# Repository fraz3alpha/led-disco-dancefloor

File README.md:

# led-disco-dancefloor

Welcome to the LED Disco Dance Floor project!

As seen at:

- Oggcamp 2017
- LJC Mad Scientists 2016

## Overview

The dancefloor project was conceived, as all good ideas are, at the pub.
The plan was to create a fully illuminated dancefloor, as a surpise, for the
wedding of two of my good friends; Gav & Anna.

The timeline from conception (pub) to completion (wedding) was roughly 8 months
between July of 2013 and the wedding in February 2014. Ideas were bounced around,
rejected, reworked, costed, rejected, reworked, and reworked some more over the
summer, and construction began in earnest November, and continued for 3 solid
months.

The result was a dancefloor consisting of 432 illuminated tiles, each 6"x6" (
because wood comes in feet and inches) creating an usable dancing area of 12'x9'.
The dancefloor was split into 9 modules (for transportation reasons), each coming
in at 4'x3' and about 15kg.

Patterns were created via a connected laptop via the included python program
to be displayed on each module by an ATMega328 microcontroller & TLC5940 constant
current LED drivers.

## The Software

The python software is available in `software/controller/`, and can be run with
or without an attached dancefloor for demonstration and testing purposes.

The software makes use of the **pygame** library to read input from connected joypads
and keyboards, as well as draw the GUI and handle the framerate. If a dancefloor
is connected, **pyserial** is used to send the data at 1Mbps

## The PCB & Firmware

The PCB is relatively simple and is only concerned with the action of parsing
incoming data via a serial connection and displaying it on the 48 connected RGB
LEDs. An ATMega328 is used as the microcontroller, and 3xTLC5940 ICs are used
to drive 16 LEDs each. Each of the Red, Green, and Blue LEDs are strobed, and
the switching is handled via 3 p-channel MOSFETs.

The firmware is written to be flashed using the Arduino IDE for convenience, but
uses very few of the Arduino library convenience functions (`random()`, which is
used in the failsafe backup pattern, being the exception) as most of the tight
loop is highly optimised for speed.

## Power

The entire dancefloor runs off 5v, and requires a high current power supply -
roughly 2.5A per module. An old ATX power supply with all the 5v rails tied
together has proved very reliable.

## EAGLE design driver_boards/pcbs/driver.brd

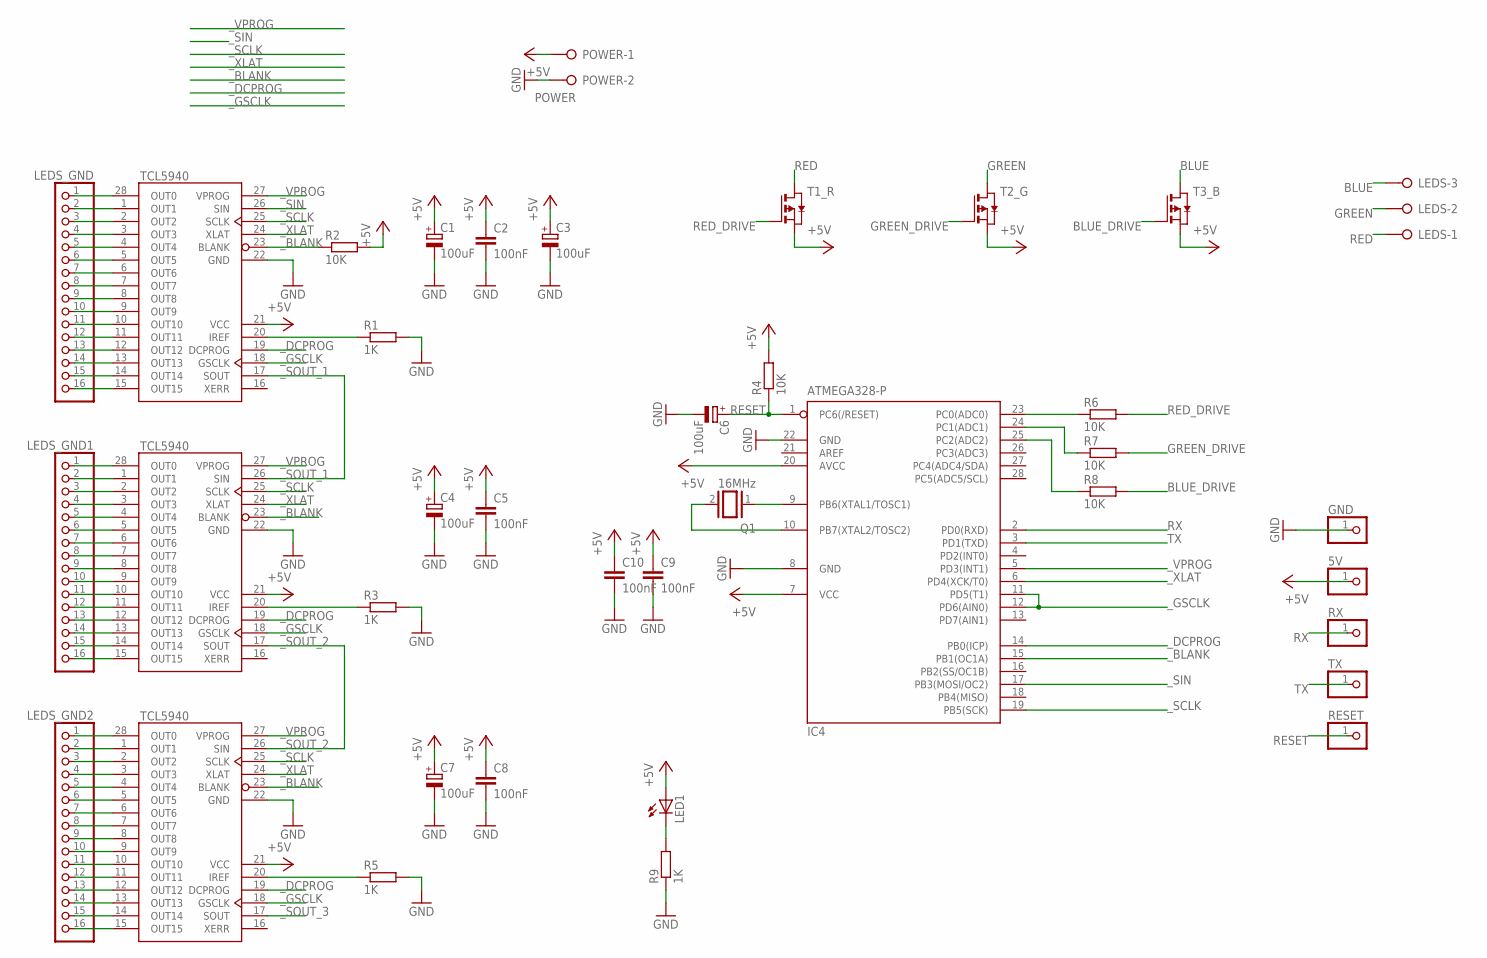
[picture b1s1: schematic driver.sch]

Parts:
5V: PINHD-1X1; 1X01
C1, C3, C4, C6, C7: 100uF; E2,5-6
C2, C5, C8, C9, C10: 100nF; C025-025X050
GND: PINHD-1X1; 1X01
IC4: ATMEGA328-P; DIL28-3
LED1: LED5MM
LEDS: W237-3E
LEDS_GND, LEDS_GND1, LEDS_GND2: PINHD-1X16; 1X16
POWER: POWER; W237-132
Q1: 16MHz; QS
R1, R3, R5, R9: 1K; M0805
R2, R4, R6, R7, R8: 10K; M0805
RESET: PINHD-1X1; 1X01
RX: PINHD-1X1; 1X01
T1_R, T2_G, T3_B: PMOSSOT23; SOT-23
TCL5940_1: TCL5940; DIP28
TLC5940_2, TLC5940_3: TCL5940; DIP28
TX: PINHD-1X1; 1X01

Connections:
+5V: 5V.1, C1.+, C2.1, C3.+, C4.+, C5.1, C7.+, C8.1, C9.1, C10.1, IC4.7 (VCC), IC4.20 (AVCC), LED1.A, POWER.1, R2.2, R4.2, T1_R.2 (S), T2_G.2 (S), T3_B.2 (S), TCL5940_1.21 (VCC), TLC5940_2.21 (VCC), TLC5940_3.21 (VCC)
BLUE: LEDS.3, T3_B.1 (D)
BLUE_DRIVE: R8.2, T3_B.3 (G)
GND: C1.-, C2.2, C3.-, C4.-, C5.2, C6.-, C7.-, C8.2, C9.2, C10.2, GND.1, IC4.8 (GND), IC4.22 (GND), POWER.2, R1.2, R3.2, R5.2, R9.1, TCL5940_1.22 (GND), TLC5940_2.22 (GND), TLC5940_3.22 (GND)
GREEN: LEDS.2, T2_G.1 (D)
GREEN_DRIVE: R7.2, T2_G.3 (G)
unnamed: R1.1, TCL5940_1.20 (IREF)
unnamed: LEDS_GND.1, TCL5940_1.28 (OUT0)
unnamed: LEDS_GND.2, TCL5940_1.1 (OUT1)
unnamed: LEDS_GND.3, TCL5940_1.2 (OUT2)
unnamed: LEDS_GND.4, TCL5940_1.3 (OUT3)
unnamed: LEDS_GND.5, TCL5940_1.4 (OUT4)
unnamed: LEDS_GND.6, TCL5940_1.5 (OUT5)
unnamed: LEDS_GND.7, TCL5940_1.6 (OUT6)
unnamed: LEDS_GND.8, TCL5940_1.7 (OUT7)
unnamed: LEDS_GND.9, TCL5940_1.8 (OUT8)
unnamed: LEDS_GND.10, TCL5940_1.9 (OUT9)
unnamed: LEDS_GND.11, TCL5940_1.10 (OUT10)
unnamed: LEDS_GND.12, TCL5940_1.11 (OUT11)
unnamed: LEDS_GND.13, TCL5940_1.12 (OUT12)
unnamed: LEDS_GND.14, TCL5940_1.13 (OUT13)
unnamed: LEDS_GND.15, TCL5940_1.14 (OUT14)
unnamed: LEDS_GND.16, TCL5940_1.15 (OUT15)
unnamed: R3.1, TLC5940_2.20 (IREF)
unnamed: LEDS_GND1.1, TLC5940_2.28 (OUT0)
unnamed: LEDS_GND1.2, TLC5940_2.1 (OUT1)
unnamed: LEDS_GND1.3, TLC5940_2.2 (OUT2)
unnamed: LEDS_GND1.4, TLC5940_2.3 (OUT3)
unnamed: LEDS_GND1.5, TLC5940_2.4 (OUT4)
unnamed: LEDS_GND1.6, TLC5940_2.5 (OUT5)
unnamed: LEDS_GND1.7, TLC5940_2.6 (OUT6)
unnamed: LEDS_GND1.8, TLC5940_2.7 (OUT7)
unnamed: LEDS_GND1.9, TLC5940_2.8 (OUT8)
unnamed: LEDS_GND1.10, TLC5940_2.9 (OUT9)
unnamed: LEDS_GND1.11, TLC5940_2.10 (OUT10)
unnamed: LEDS_GND1.12, TLC5940_2.11 (OUT11)
unnamed: LEDS_GND1.13, TLC5940_2.12 (OUT12)
unnamed: LEDS_GND1.14, TLC5940_2.13 (OUT13)
unnamed: LEDS_GND1.15, TLC5940_2.14 (OUT14)
unnamed: LEDS_GND1.16, TLC5940_2.15 (OUT15)
unnamed: R5.1, TLC5940_3.20 (IREF)
unnamed: LEDS_GND2.1, TLC5940_3.28 (OUT0)
unnamed: LEDS_GND2.2, TLC5940_3.1 (OUT1)
unnamed: LEDS_GND2.3, TLC5940_3.2 (OUT2)
unnamed: LEDS_GND2.4, TLC5940_3.3 (OUT3)
unnamed: LEDS_GND2.5, TLC5940_3.4 (OUT4)
unnamed: LEDS_GND2.6, TLC5940_3.5 (OUT5)
unnamed: LEDS_GND2.7, TLC5940_3.6 (OUT6)
unnamed: LEDS_GND2.8, TLC5940_3.7 (OUT7)
unnamed: LEDS_GND2.9, TLC5940_3.8 (OUT8)
unnamed: LEDS_GND2.10, TLC5940_3.9 (OUT9)
unnamed: LEDS_GND2.11, TLC5940_3.10 (OUT10)
unnamed: LEDS_GND2.12, TLC5940_3.11 (OUT11)
unnamed: LEDS_GND2.13, TLC5940_3.12 (OUT12)
unnamed: LEDS_GND2.14, TLC5940_3.13 (OUT13)
unnamed: LEDS_GND2.15, TLC5940_3.14 (OUT14)
unnamed: LEDS_GND2.16, TLC5940_3.15 (OUT15)
unnamed: LED1.K (C), R9.2
unnamed: IC4.9 (PB6(XTAL1/TOSC1)), Q1.1
unnamed: IC4.10 (PB7(XTAL2/TOSC2)), Q1.2
unnamed: IC4.23 (PC0(ADC0)), R6.1
unnamed: IC4.24 (PC1(ADC1)), R7.1
unnamed: IC4.25 (PC2(ADC2)), R8.1
RED: LEDS.1, T1_R.1 (D)
RED_DRIVE: R6.2, T1_R.3 (G)
RESET: C6.+, IC4.1 (PC6(/RESET)), R4.1, RESET.1
RX: IC4.2 (PD0(RXD)), RX.1
TX: IC4.3 (PD1(TXD)), TX.1
_BLANK: IC4.15 (PB1(OC1A)), R2.1, TCL5940_1.23 (BLANK), TLC5940_2.23 (BLANK), TLC5940_3.23 (BLANK)
_DCPROG: IC4.14 (PB0(ICP)), TCL5940_1.19 (DCPROG), TLC5940_2.19 (DCPROG), TLC5940_3.19 (DCPROG)
_GSCLK: IC4.11 (PD5(T1)), IC4.12 (PD6(AIN0)), TCL5940_1.18 (GSCLK), TLC5940_2.18 (GSCLK), TLC5940_3.18 (GSCLK)
_SCLK: IC4.19 (PB5(SCK)), TCL5940_1.25 (SCLK), TLC5940_2.25 (SCLK), TLC5940_3.25 (SCLK)
_SIN: IC4.17 (PB3(MOSI/OC2)), TCL5940_1.26 (SIN)
_SOUT_1: TCL5940_1.17 (SOUT), TLC5940_2.26 (SIN)
_SOUT_2: TLC5940_2.17 (SOUT), TLC5940_3.26 (SIN)
_SOUT_3: TLC5940_3.17 (SOUT)
_VPROG: IC4.5 (PD3(INT1)), TCL5940_1.27 (VPROG), TLC5940_2.27 (VPROG), TLC5940_3.27 (VPROG)
_XLAT: IC4.6 (PD4(XCK/T0)), TCL5940_1.24 (XLAT), TLC5940_2.24 (XLAT), TLC5940_3.24 (XLAT)

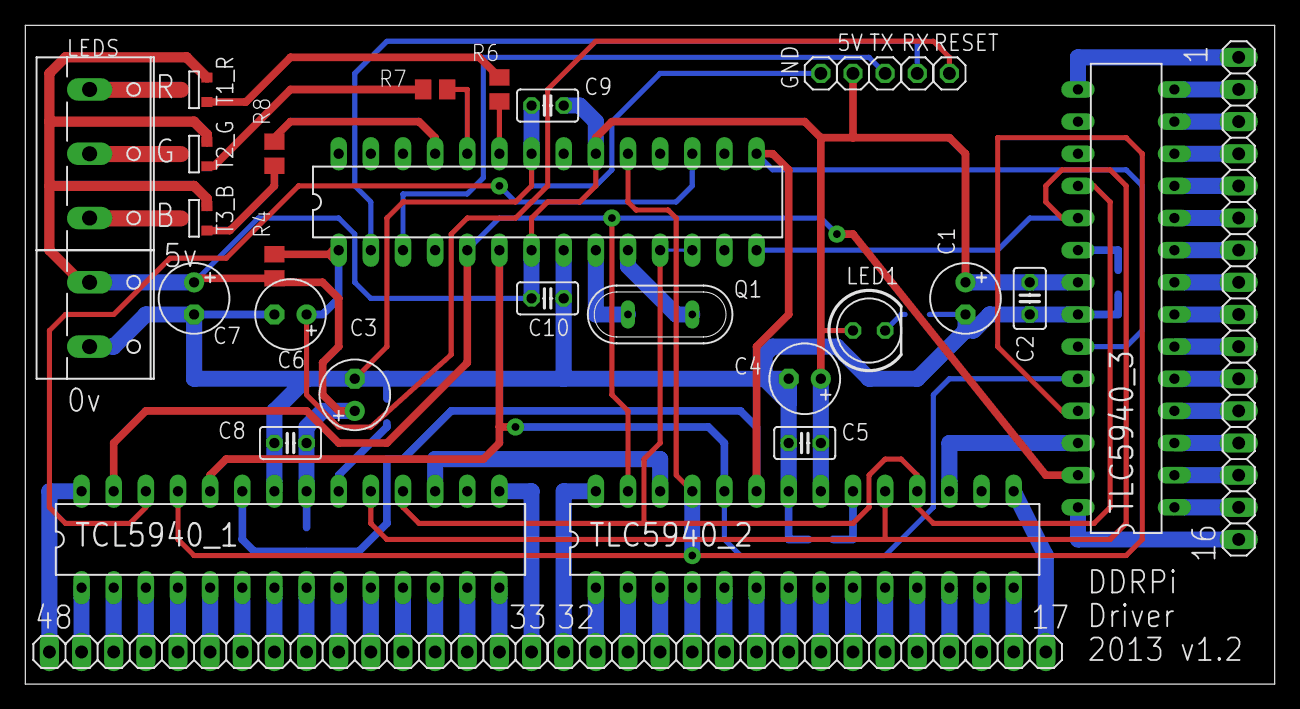
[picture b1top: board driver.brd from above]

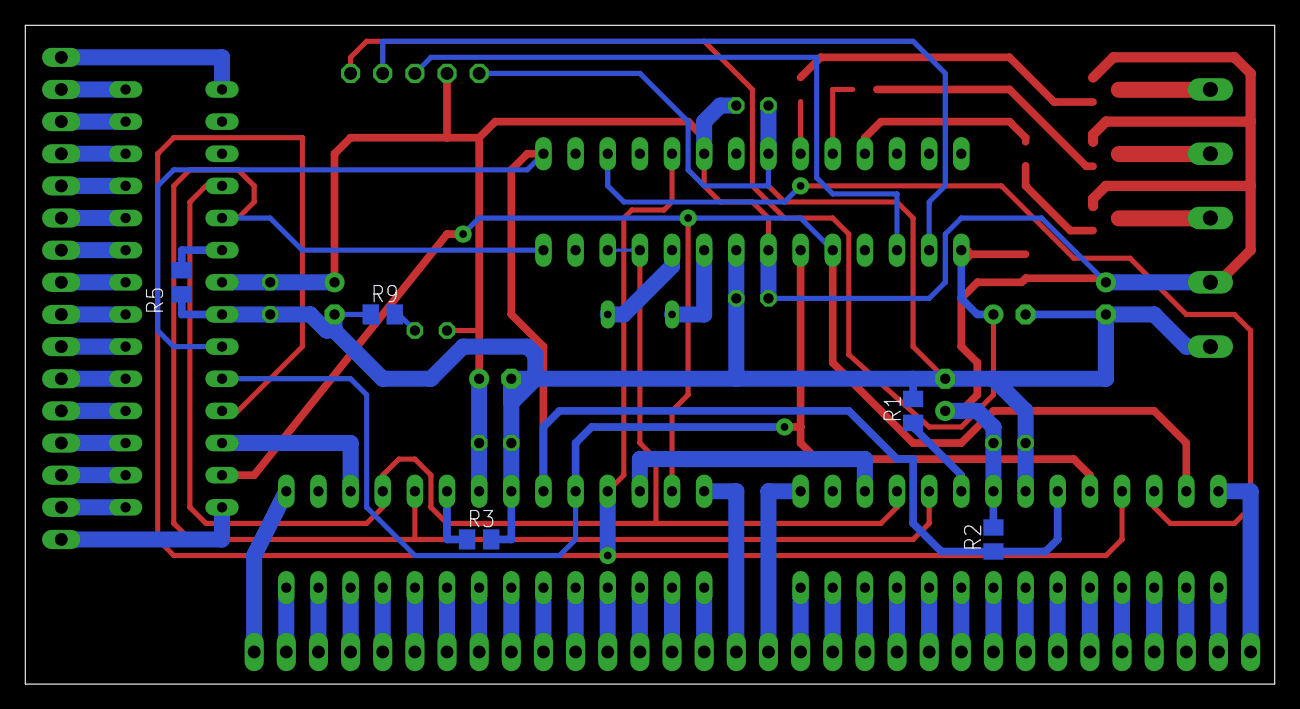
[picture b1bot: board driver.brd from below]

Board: 2 copper layers, 98.7 x 52.1 mm, 38 parts (5 on the bottom side), 77 nets.

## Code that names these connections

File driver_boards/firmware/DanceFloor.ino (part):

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//Gray Scale Depth for the PWM on TLC5940
#define Gray_Scale_Depth 4095

//GSCLK an PD6 (Arduino Pin 6)
#define GSCLK_Low       PORTD &=  ~(1 << 6)
#define GSCLK_High      PORTD |=   (1 << 6)

//XLAT an PD4 (Arduino Pin 4)
#define XLAT_Low       PORTD &=  ~(1 << 4)
#define XLAT_High      PORTD |=   (1 << 4)

//GSCK an PD5 (Arduino Pin 5)
#define GSCK_Low       PORTD &=  ~(1 << 5)
#define GSCK_High      PORTD |=   (1 << 5)

//VPRG an PD3 (Arduino Pin 3)
#define VPRG_Low       PORTD &=  ~(1 << 3)
#define VPRG_High      PORTD |=   (1 << 3)

//BLANK an PB1 (Arduino Pin 9)
#define BLANK_Low       PORTB &=  ~(1 << 1)
#define BLANK_High      PORTB |=   (1 << 1)

//SCLK an PB5 (Arduino Pin 13)
#define SCLK_Low       PORTB &=  ~(1 << 5)
#define SCLK_High      PORTB |=   (1 << 5)

//MOSI an PB3 (Arduino Pin 11)
#define MOSI_Low       PORTB &=  ~(1 << 3)
#define MOSI_High      PORTB |=   (1 << 3)

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void setup()   
{               
  // Set pins as inputs or outputs
  // Setup the SPI connection pins and the TLC5940 BLANK signal on PORTB
  DDRB |= (1<<1)  | (1<<2)  | (1<<3) | (1<<5) ; // BLANK, SS, MOSI, SCLK as OUTPUTS
  // Setup the remainder of the TLC5940 signal pins on PORTD
  DDRD |= (1<<3)  | (1<<4) |  (1<<6) | (1<<7) ; // VPRG, XLAT, GSCLK, Debug as OUTPUTS
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
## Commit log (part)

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2014-04-04 Initial commit of Firmware
    Initial firmware based on the code from solderlab.de
    with various changes , including pins used, number of
    columns strobed, and generation of random patterns
    when there is no input data
2014-04-04 Eliminate LED flicker when cycling through colours
    Closes #1 - whereby LEDs have a noticeable flicker when cycling
    through the random colours.
    - Move the call to random() so that it is called at most once
    per loop, and that the time take to calculate new values is
    spread out, reducing the time paused when creating a new
    set of pixel colours
2014-04-04 Move controller code to its own directory
    Created software/controller to contain the code that
    drives the floor so that it isn't mixed in with other
    resources such as design documentation, firmware etc..
2014-04-09 Fixed random flickering bug when received data via UART
    Previously the LEDs would flash everytime a new frame
    was received due to insufficient processing time being
    available.
    I have increased the time between switching between each
    LED colour (effectively doubled) from a on time of ~ 0.5ms
    to 1ms. This reduces the amount of time spent in interrupt
2014-04-27 Updated python code to the V2 work in progress
    - Including:
    New playlist mechanism for automatic cycling of plugins
    Multiple plugin directories (currently hard coded)
    --testmode for those without a floor, and who don't want
    to mess around with config files
    A nice GUI to show what is going on (can be disabled
2014-04-27 Add basic README for the python controller code
2014-04-27 Resolve path of relative plugin directories relative to root
    - Change the way the plugin directories are resolved,
    instead of being relative to the current working
    directory they are now relative to the root of
    the main DDRPi script, meaning that it can be invoked
    from anywhere, no longer just in the root directory
2014-04-27 Add initial version of the patterns plugin
    - Ported the existing PatternsVisualisationPlugin
    to the new format and added a directory of its
    own to store the various CSV files in
2014-04-27 Conform with Python 3 division
    Ensure that parameters that need to be ints, are ints
2014-04-27 Change print calls to print() calls where necessary
2014-04-27 Remove reference to itertools.next() which has gone in python 3
    - Replace .next() with next(..) which works in python 2.6+
2014-04-27 Add logger and remove reference to print()
    - Removed reference to print(), with all text output now
    being handled by a Logger, set by default to Info level
2014-04-27 Switch dict.iteritems() to .items() for python 3
    - .iteritems() was removed in python 3, so switch to using
    .items() which is just as good for our usage
2014-04-27 Switch to use standard logging
    - My logger clashed with the built-in one, so switch to using that
2014-04-27 Remove another reference to iteritems()
2014-04-27 Initial commit of SpeedingBlobs plugin
2014-04-27 Initial commit of scrolling text plugin and text writing lib
    - Initial commit of scrolling text plugin, with a hardcoded
    scrolling message
    - Add basic text drawing methods to the FloorCanvas object
    - Fix bug in FloorCanvas.is_in_range()
2014-04-28 Add basic keyboard > joystick button mapping
    - Enable testing of plugins that take input without connected
    joypads by mapping keyboard input events to joystick events
    - Renamed handle method in DiscoFloor plugin so that it receives
    events
2014-04-28 Refactor DiscoFloor Plugin to run at a higher framerate
    - The DiscoFloorVisualisationPlugin now runs at 25fps,
    but still only updates the colours at the specified
    rate. This means that input events are taken off the
    queue in a more timely manner, and the input feels
    more responsive
2014-04-28 Add PipeOutput class
    - Add pipe output class, and refactor it and the SerialOutput
    to have a common superclass as they both perform the
    conversion logic
    - Add sample config stanza for the PipeOutput
    - Add an initial checkin of the FloorSimulator code
    - Add a method to the layout to determine the correct order to
2014-04-28 Added --playlist option, and configurable plugins
    - A playlist can now be passed in on the command line using
    the --playlist argument.
    - A playlist is a yaml file consisting of a list of plugins
    in the playlist, and any configuration options for them.
    All plugins support the duration: attribute, and it is
    a time given in seconds
2014-04-28 Change a few things to be Python 3 compliant
2014-04-30 Rewrite apply() without reduce()
    - Removed the use of reduce() which isn't a first class function
    in python 3, and replaced it with a simple equivalent implementation
2014-05-02 Set converter on SerialOutput output classes
    - Missing call to .set_output_converter() when creating
    SerialOutput instances
2014-05-02 Add extra colours, check for tuples and convert to ints when setting pixels
    - Added constants for CYAN, MAGENTA and YELLOW
    - Added check in set_pixel() to see if the colour is given as a tuple,
    if so then the tuple is converted automatically into an int
2014-05-02 Create stable spash screen for the DiscoFloor Plugin
    - Change the draw_splash() on the DiscoFloor plugin
    to use a constant seed for random() so that the
    splash screen is constant without being hardcoded
2014-05-02 Add splash screen to the ScrollingText plugin
2014-05-02 Add splash screen to the WavyBlob plugin
2014-05-02 Catch errors from parsing missing attributes in the SineWave plugin
    - Add catching AttributeError to the config parsing, which
    we get when the config hasn't been set for that attribute
2014-05-03 Don't auto advance plugins of type ALL
    - If the primary playlist is selected, the one that contains
    all the plugins, set it to not auto-advance so that the
    plugin remains static
2014-05-03 Initial commit of spinning wheel plugin
    - Like the Mac OS spinngin wheel of death, it cycles
    around, varying the hue as it goes
2014-05-03 Hide time remaining value in GUI when plugin doesn't auto advance
    - When the playlist doesn't automatically move to the next plugin
    the time remaining doesn't make any sense, so hide that
    bit of information in the case that auto_advance is false
2014-05-03 Add Left/Right arrows for navigating plugins in a playlist
    - Replicate UI elements that were already present for navigating
    through available playlists
2014-05-04 Add splash screen to SoundToLight Plugin
2014-05-06 Hardened calling plugin frame drawing methods
    - Added try: except: around calling plugin .draw_frame()
    and .draw_splash()
    - In case of failure, draw a default message - currently
    a red screen of death
    - Also change the menu scrolling code to draw a bar, not
    the arrows as previously
2014-05-10 Add brightness control to Disco Floor plugin
    - D-pad up and down now controls the brightness (10 steps)
    and d-pad left and right regenerate a new set of colours
    (useful when the pattern is stopped (0 FPS)
    Resolves #6
2014-05-10 Add Spotlight plugin
    - Add plugin to have user controlled circles on the floor, with variable
    brightness.
    - Added draw_circle method to the floor canvas
    Resolves #7
2014-05-18 Start a plugin automatically on boot
    - In the absence of any specific plugin being selected using
    --plugin, or a playlist being requested using --playlist,
    start one of the default plugins (only DiscoFloor at the moment)
    or failing that, just start the all_plugins playlist
    Fixes #9
2014-05-18 Catch exceptions loading plugins and skip them
    - In the case where a plugin can't be loaded for any reason
    (e.g. a dependent module is not available, or there is a
    syntax error), then skip over that plugin
    Fixes #10
2014-05-18 Read multiple --playlist arguments from the command line
    - Multiple calls to set --playlist now append to the internal
    list and all are available to select from. The first one is
    the default
    Fixes #11
2014-05-18 Print error when the plugin can't draw a frame
2014-05-19 Add frequency binning algorithm and fire colours
    - Added option to chose between 'linear' and 'exponetial'
    frequency binning algorithms, mapped to X&Y on a joypad
    - Added Phil's fire colours
    Fixes #3
2014-05-20 Initial commit of Camera streaming plugin
    - Doesn't have a lot of use, but see the world in
    highly pixelated form! On your dance floor!
2014-05-24 Handle exception correctly
2014-05-24 Added missing logging import
2014-05-24 Add Fireworks display plugin
2014-05-24 Add floor rotation functionality
    - The floor output can be rotate by adding
    system:floor_rotation: 0|1|2|3
    to the config file. Each increment rotates the floor output
    by 90 degrees
    Fixes #2
2014-05-24 Removed some chatty debug messages
2014-05-24 Add Pong and Tetris
2014-05-24 Improve firework explosions
2014-05-25 Guard against div/0 error
2014-05-25 Add alpha channel setting to set_pixel
    - The fireworks plugin added the concept of merging pixels, which
    effectively drew some pixels with an alpha channel so that what
    was behind was still visible. Move this code to the floorcanvas
    library so that everyone can use it, and add it as an optional
    parameter to set_pixel. Default is 1.0, i.e. no alpha
2014-05-25 Added new playlist, and updated some plugins to take extra config
2014-05-25 Added explosion option
    - Along side fireworks, just general random explosions
    can now also be shown. Switchable with LB, or a config
    parameter
2014-05-27 Add text customisations
    - In order to display some names on the Love Heart plugin we
    need to shorten some of the letters. Here werovide a mechanism
    to pass in the character definitions so that we can draw
    whatever seems reasonable.
    - Add two specific text drawing functions for Naomi and Phil
    - Add the Phil & Naomi message to the playlist
2014-05-28 Made Patterns plugin configurable
    - Taken the existing pattern configurations and added them into
    and internal repository, so that they can be selected from
    by appropriate configuration in a playlist. In the absence of
    any specific patterns listed, all the patterns are added
    - Also added a couple of patterns to the sample playlist
    Fixes #13
2014-05-28 Fixed #12 - Tetris crash when UP is the first button pressed
    - Pressing UP as the first button failed because the repeat_axis
    wasn't set up for buttons that had no effect. We now skip
    past the check if we haven't set the axis
2015-09-26 Fixed always writing the upper name for the LoveHeart
    - The upper_name parameter was always written for both the upper
    and lower names
2015-09-26 Reformatted all code to be PEP-8 compliant
    - Lots of tabs have been replaced with spaces, meaning that most
    files have ended up with changes in them
    - No functional changes should have occurred during this commit
2015-09-26 Added initial filter support to Serial Output
    - Now we can add filters to the output getting sent to the serial port,
    initially:
    ClearFilter
    NegativeFilter
    NeutralDensityFilter
    - Filters configured in config.yaml in system > filters
2016-03-21 Initial commit of Twitter Playlist functionality
    - Configuration allows a Twitter playlist to be created, which will
    start plugins based on Tweet requests from people.
    - We send a nice message to say we've received that request, and then
    Tweet again when we start that plugin.
    - There is no explicit code to reconnect to Twitter if the connection
    drops, and I don't as yet know what the API does if this happens.
2016-03-23 pluginmode.add_playlist() now returns index of added playlist
2016-03-23 Sine Wave visualisation now calculates the height based on the size of the canvas
    - The amplitude of the sinewave is now dynamic based on floor size:
    amplitude = (canvas.get_height / 2) -1
2016-03-23 Add Solid Colour visualisation
    - Good for testing, or flooding the room with light
2016-03-23 Tidy up GUI - remove cross and give time in seconds
2016-03-23 Catch exceptions from Tweets
2016-03-23 Round playlist time remaining down to seconds, and don't display negative numbers
2016-03-23 Add Twitter requests for scrolling text
    - Scrolling text now available, and will display anything after the
    "scrolltext" keyword request
2016-03-23 Add mechanism to turn off Twitter playlist in the config
